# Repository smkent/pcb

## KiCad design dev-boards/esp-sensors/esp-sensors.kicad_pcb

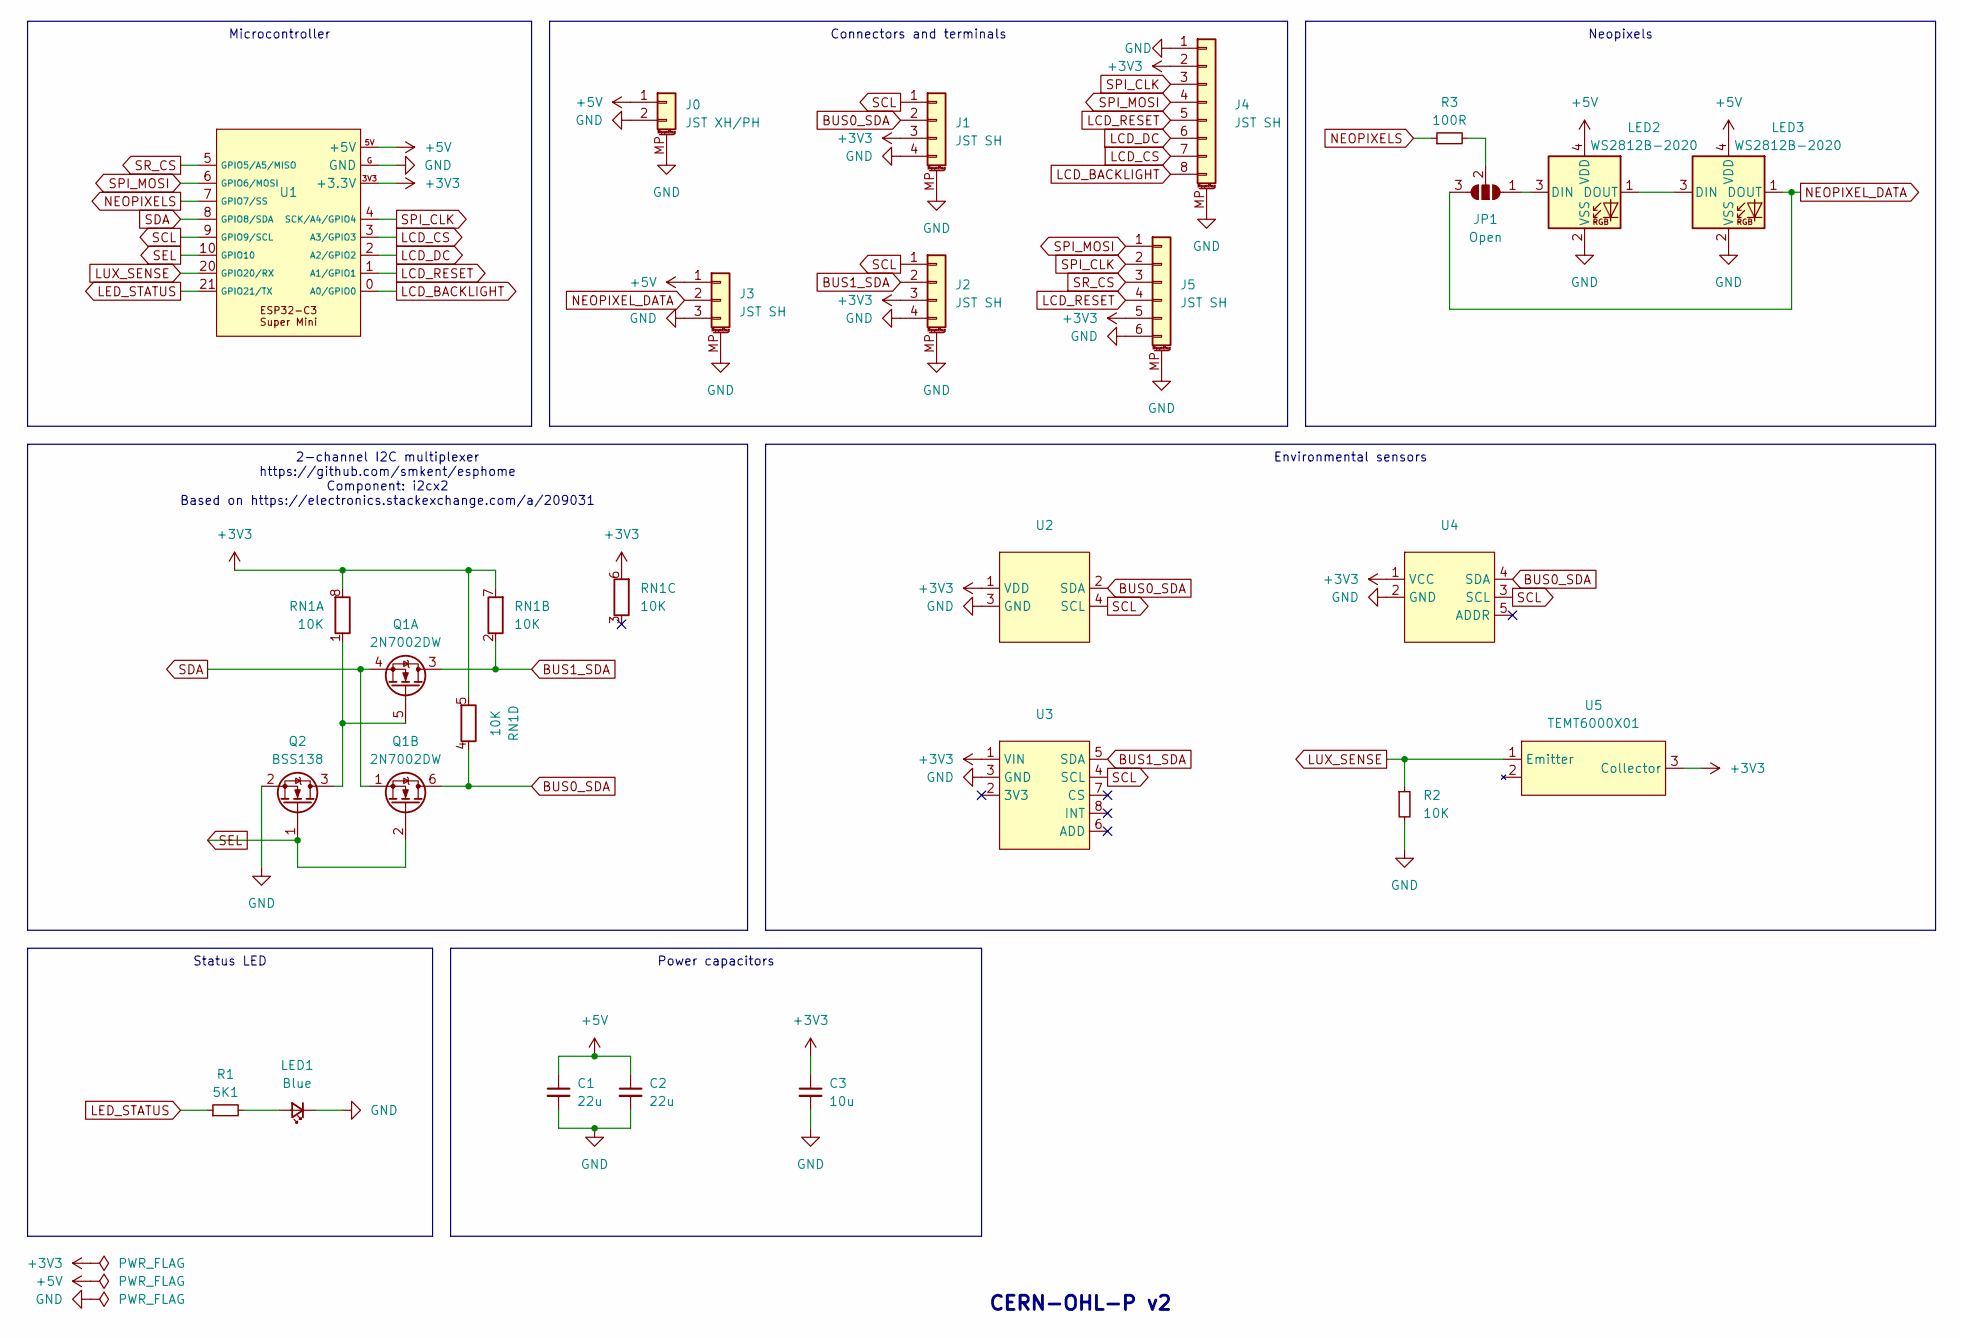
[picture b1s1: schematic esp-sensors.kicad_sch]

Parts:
C1, C2: 22u; C_0805_2012Metric_Pad1.18x1.45mm_HandSolder
C3: 10u; C_0603_1608Metric_Pad1.08x0.95mm_HandSolder
J0: JST XH/PH; Conn_Combo_JST-1x02-XH_PH-SMD-pad2gnd
J1, J2: JST SH; JST_SH_SM04B-SRSS-TB_1x04-1MP_P1.00mm_Horizontal
J3: JST SH; JST_SH_SM03B-SRSS-TB_1x03-1MP_P1.00mm_Horizontal
J4: JST SH; JST_SH_SM08B-SRSS-TB_1x08-1MP_P1.00mm_Horizontal
J5: JST SH; JST_SH_SM06B-SRSS-TB_1x06-1MP_P1.00mm_Horizontal
JP1: Open; SolderJumper-3_P1.3mm_Open_RoundedPad1.0x1.5mm
LED1: Blue; LED_0603_1608Metric_Pad1.05x0.95mm_HandSolder_simple
LED2, LED3: WS2812B-2020; LED-SMD_4P-L2.0-W2.0-BR-1
Q1: 2N7002DW; SOT-23-6; LCSC Part C5190214
Q2: BSS138; SOT-23
R1: 5K1; R_0603_1608Metric_Pad0.98x0.95mm_HandSolder_simple
R2: 10K; R_0603_1608Metric_Pad0.98x0.95mm_HandSolder_simple
R3: 100R; R_0603_1608Metric_Pad0.98x0.95mm_HandSolder
RN1: 10K; R_Array_Convex_4x0603
U1: ESP32-C3-Super-Mini-Castellated-SMD
U2: PinSocket_1x04_P2.54mm_Horizontal_descending_simple
U3: PinSocket_1x08_P2.54mm_Horizontal_descending_simple
U4: PinSocket_1x05_P2.54mm_Horizontal_simple
U5: TEMT6000X01; SENSORS-SMD_TEMT6000X01_HandSolder; LCSC Part C94098

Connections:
+3V3: C3.1, J1.3, J2.3, J4.2, J5.5, RN1.5 (R4.2), RN1.6 (R3.2), RN1.7 (R2.2), RN1.8 (R1.2), U1.3V3 (+3.3V), U2.1 (VDD), U3.1 (VIN), U4.1 (VCC), U5.3 (Collector)
+5V: C1.1, C2.1, J0.1, J3.1, LED2.4 (VDD), LED3.4 (VDD), U1.5V (+5V)
BUS0_SDA: J1.2, Q1.6 (D), RN1.4 (R4.1), U2.2 (SDA), U4.4 (SDA)
BUS1_SDA: J2.2, Q1.3 (D), RN1.2 (R2.1), U3.5 (SDA)
GND: C1.2, C2.2, C3.2, J0.2, J0.MP (MountPin), J1.4, J1.MP (MountPin), J2.4, J2.MP (MountPin), J3.3, J3.MP (MountPin), J4.1, J4.MP (MountPin), J5.6, J5.MP (MountPin), LED1.1 (K), LED2.2 (VSS), LED3.2 (VSS), Q2.2 (S), R2.2, U1.G (GND), U2.3 (GND), U3.3 (GND), U4.2 (GND)
LCD_BACKLIGHT: J4.8, U1.0 (A0/GPIO0)
LCD_CS: J4.7, U1.3 (A3/GPIO3)
LCD_DC: J4.6, U1.2 (A2/GPIO2)
LCD_RESET: J4.5, J5.4, U1.1 (A1/GPIO1)
LED_STATUS: R1.1, U1.21 (GPIO21/TX)
LUX_SENSE: R2.1, U1.20 (GPIO20/RX), U5.1 (Emitter)
NEOPIXELS: R3.1, U1.7 (GPIO7/SS)
NEOPIXEL_DATA: J3.2, JP1.3 (B), LED3.1 (DOUT)
unnamed: JP1.1 (A), LED2.3 (DIN)
unnamed: JP1.2 (C), R3.2
unnamed: LED1.2 (A), R1.2
unnamed: LED2.1 (DOUT), LED3.3 (DIN)
unnamed: Q1.5 (G), Q2.3 (D), RN1.1 (R1.1)
SCL: J1.1, J2.1, U1.9 (GPIO9/SCL), U2.4 (SCL), U3.4 (SCL), U4.3 (SCL)
SDA: Q1.1 (S), Q1.4 (S), U1.8 (GPIO8/SDA)
SEL: Q1.2 (G), Q2.1 (G), U1.10 (GPIO10)
SPI_CLK: J4.3, J5.2, U1.4 (SCK/A4/GPIO4)
SPI_MOSI: J4.4, J5.1, U1.6 (GPIO6/MOSI)
SR_CS: J5.3, U1.5 (GPIO5/A5/MISO)

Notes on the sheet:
2-channel I2C multiplexer https://github.com/smkent/esphome Component: i2cx2 Based on https://electronics.stackexchange.com/a/209031
Environmental sensors
Microcontroller
Power capacitors
Neopixels
Status LED
Connectors and terminals
CERN-OHL-P v2

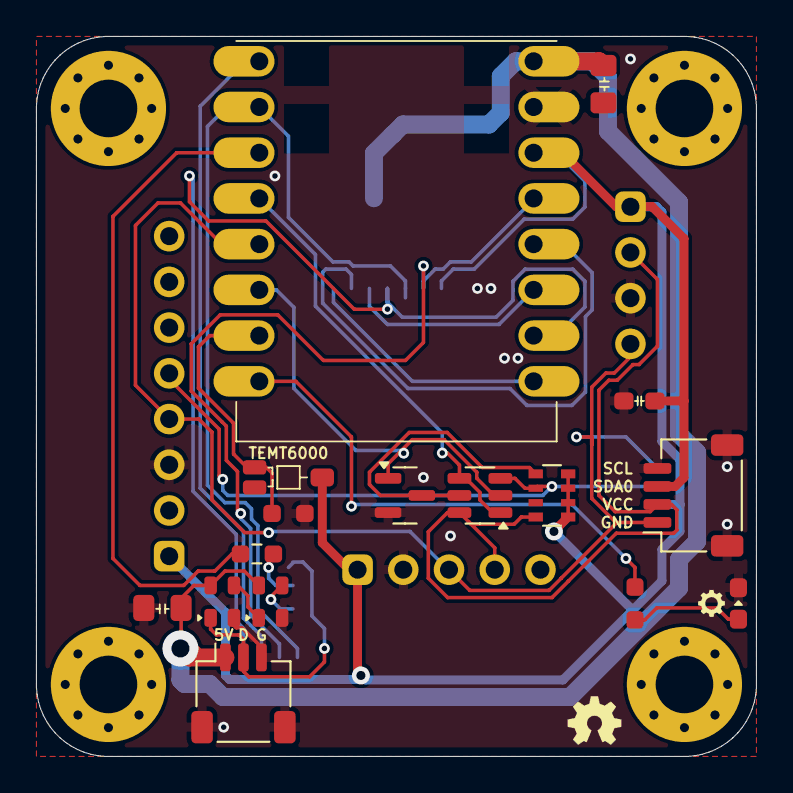
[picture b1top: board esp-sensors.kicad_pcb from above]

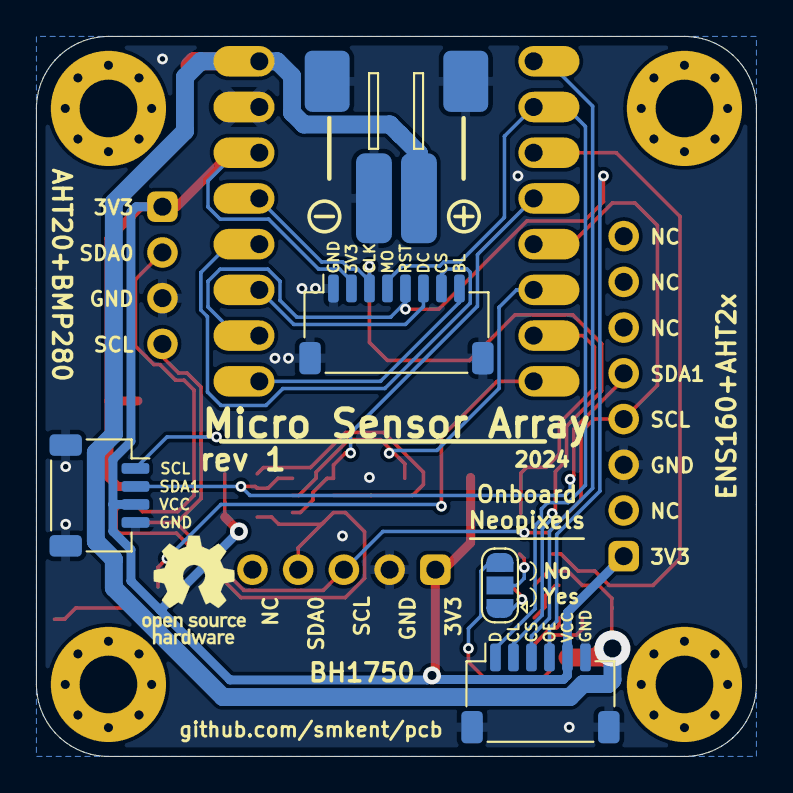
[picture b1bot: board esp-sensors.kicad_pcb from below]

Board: 2 copper layers, 40.0 x 40.0 mm, 24 parts (5 on the bottom side), 24 nets.

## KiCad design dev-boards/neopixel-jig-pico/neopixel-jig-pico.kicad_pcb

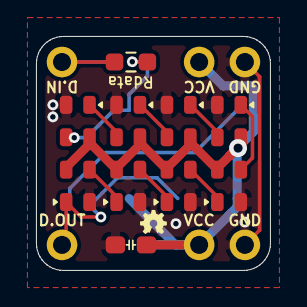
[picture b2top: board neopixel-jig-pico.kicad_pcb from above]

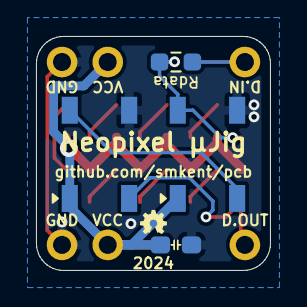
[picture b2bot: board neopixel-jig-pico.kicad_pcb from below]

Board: 2 copper layers, 13.0 x 13.0 mm, 18 parts (8 on the bottom side), 13 nets.

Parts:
C1, C2: 10u; C_0603_1608Metric_Pad1.08x0.95mm_HandSolder
D1, D2: WS2812B; LED_WS2812B_PLCC4_5.0x5.0mm_P3.2mm_simple_small_courtyard
J1, J2: Conn_01x02; PinHeader_1x02_P2.54mm_Vertical_simple
J3, J4: Conn_01x01; PinHeader_1x01_P2.54mm_simple
LED1, LED2, LED3, LED4, LED5, LED6, LED7, LED8: WS2812B-2020; LED-SMD_4P-L2.0-W2.0-BR-1
R1, R2: 100R; R_0603_1608Metric_Pad0.98x0.95mm_HandSolder

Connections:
DATA_2: LED4.1 (DOUT), LED5.3 (DIN)
DATA_IN: D1.4 (DIN), LED1.3 (DIN), R1.2, R2.2
DATA_OUT: D2.2 (DOUT), J4.1, LED8.1 (DOUT)
GND: C1.2, C2.2, D1.3 (VSS), D2.3 (VSS), J1.2, J2.2, LED1.2 (VSS), LED2.2 (VSS), LED3.2 (VSS), LED4.2 (VSS), LED5.2 (VSS), LED6.2 (VSS), LED7.2 (VSS), LED8.2 (VSS)
unnamed: D1.2 (DOUT), D2.4 (DIN)
unnamed: J3.1, R1.1, R2.1
unnamed: LED1.1 (DOUT), LED2.3 (DIN)
unnamed: LED2.1 (DOUT), LED3.3 (DIN)
unnamed: LED3.1 (DOUT), LED4.3 (DIN)
unnamed: LED5.1 (DOUT), LED6.3 (DIN)
unnamed: LED6.1 (DOUT), LED7.3 (DIN)
unnamed: LED7.1 (DOUT), LED8.3 (DIN)
VCC: C1.1, C2.1, D1.1 (VDD), D2.1 (VDD), J1.1, J2.1, LED1.4 (VDD), LED2.4 (VDD), LED3.4 (VDD), LED4.4 (VDD), LED5.4 (VDD), LED6.4 (VDD), LED7.4 (VDD), LED8.4 (VDD)

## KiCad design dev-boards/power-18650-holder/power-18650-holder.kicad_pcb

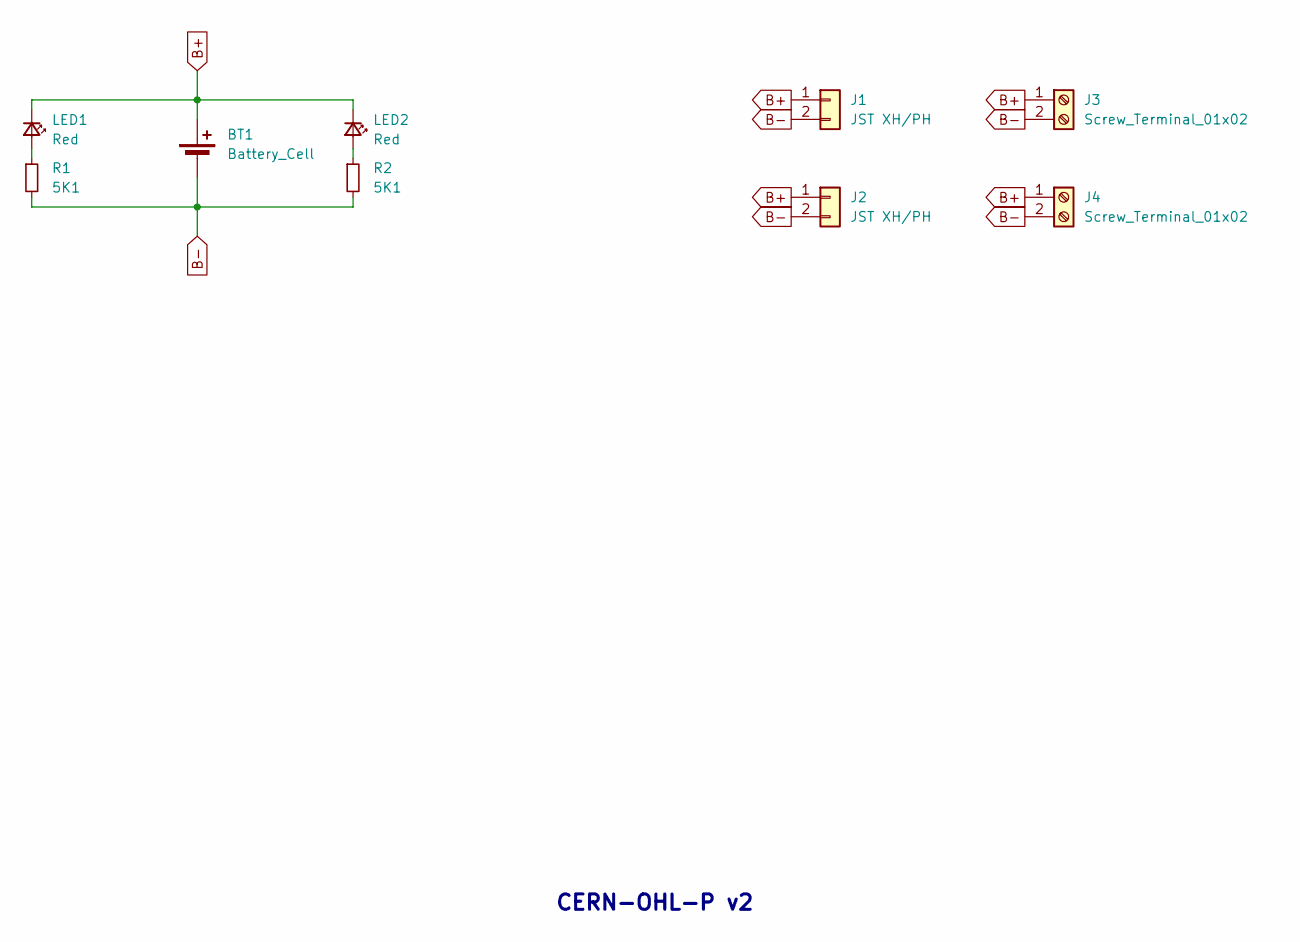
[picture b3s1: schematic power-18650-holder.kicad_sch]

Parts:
BT1: Battery_Cell; BAT-TH_18650-A5BJ001_large_vias
J1, J2: JST XH/PH; Conn_Combo_JST-1x02-XH_PH-THT-pad2gnd
J3, J4: Screw_Terminal_01x02; Conn_Combo_TerminalBlock_P3.5-P5.08_1x02_pad2gnd
LED1, LED2: Red; LED_0603_1608Metric_Pad1.05x0.95mm_HandSolder_simple; LCSC Part C2286
R1, R2: 5K1; R_0603_1608Metric_Pad0.98x0.95mm_HandSolder_simple; LCSC Part C25905

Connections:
B+: BT1.1 (+), J1.1, J2.1, J3.1, J4.1, LED1.1 (K), LED2.1 (K)
B-: BT1.2 (-), J1.2, J2.2, J3.2, J4.2, R1.2, R2.2
unnamed: LED1.2 (A), R1.1
unnamed: LED2.2 (A), R2.1

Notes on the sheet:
CERN-OHL-P v2

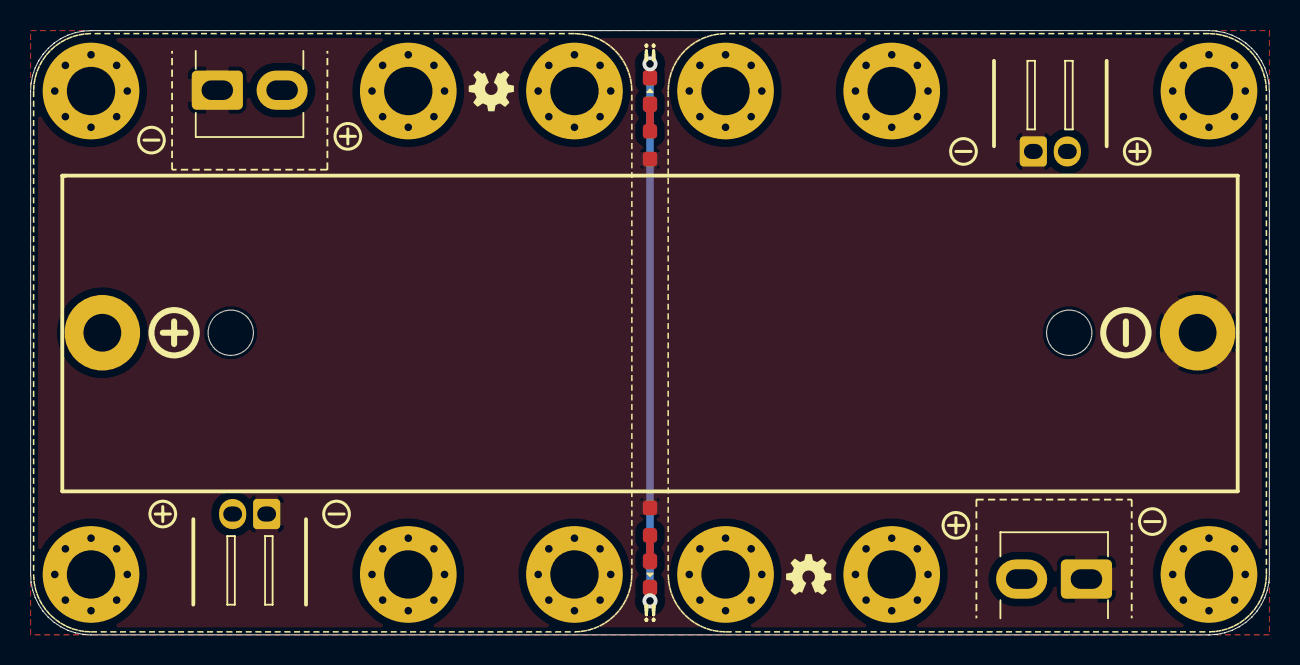
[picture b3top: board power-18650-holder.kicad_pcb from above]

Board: 2 copper layers, 82.0 x 40.0 mm, 9 parts (0 on the bottom side), 4 nets.

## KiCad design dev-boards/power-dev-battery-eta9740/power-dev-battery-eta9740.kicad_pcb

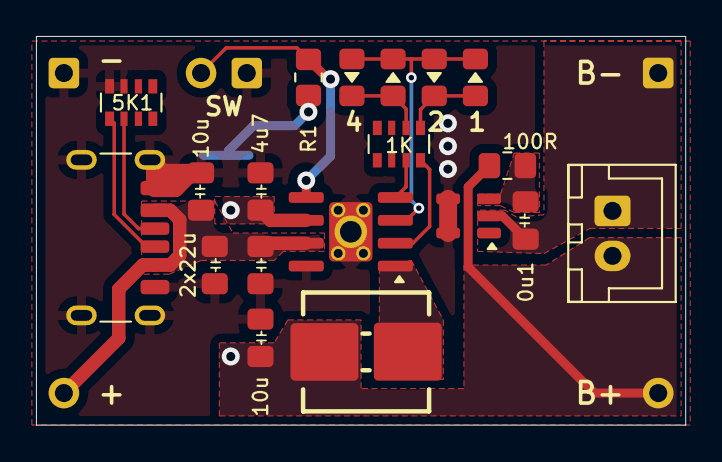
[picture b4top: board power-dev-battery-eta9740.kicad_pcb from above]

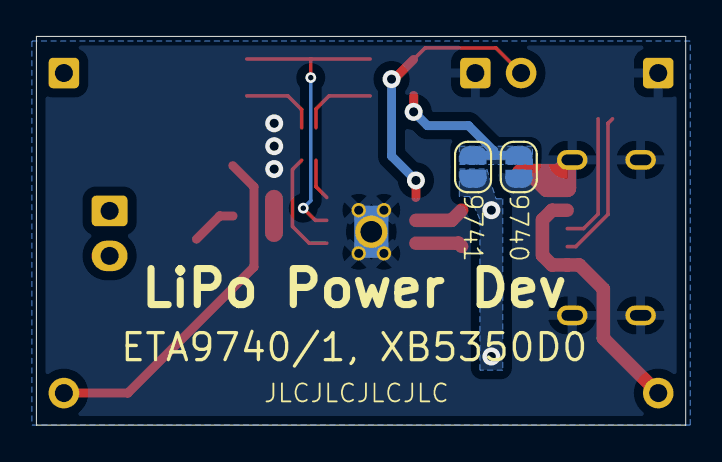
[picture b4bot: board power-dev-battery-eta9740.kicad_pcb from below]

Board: 2 copper layers, 36.1 x 21.6 mm, 26 parts (2 on the bottom side), 15 nets.

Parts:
BT1: Battery_Cell; JST_XH_B2B-XH-A_1x02_P2.50mm_Vertical_simple_pad2gnd
C1: 0.1uF; C_0805_2012Metric_Pad1.18x1.45mm_HandSolder
Cbat1: 4.7uF; C_0805_2012Metric_Pad1.18x1.45mm_HandSolder
Cin1: 10uF; C_0805_2012Metric_Pad1.18x1.45mm_HandSolder
Cout1, Cout2: 22uF; C_0805_2012Metric_Pad1.18x1.45mm_HandSolder
Cusb1: 10uF; C_0805_2012Metric_Pad1.18x1.45mm_HandSolder
J0: USB_C_Receptacle_PowerOnly_6P; USB_C_Receptacle_GCT_USB4125-xx-x_6P_TopMnt_Horizontal_hand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
J1, J3: Conn_01x01; PinHeader_1x01_P2.54mm_simple
J2, J4: Conn_01x01; PinHeader_1x01_P2.54mm_simple_square
JP1, JP2: SolderJumper_2_Open; SolderJumper-2_P1.3mm_Open_RoundedPad1.0x1.5mm
L1: 22uH; Inductor_Multi_7.0x6.6_plus
LED1, LED2, LED3, LED4: LED_0805_2012Metric_Pad1.15x1.40mm_HandSolder_simple
R1: 100K; R_0805_2012Metric_Pad1.20x1.40mm_HandSolder
R2: 100R; R_0805_2012Metric_Pad1.20x1.40mm_HandSolder
RN1: R_Pack04_Split; R_Array_Convex_4x0603
RN2: 5K1; R_Array_Convex_4x0603
SW1: SW_Push; PinHeader_1x02_P2.54mm_Vertical_simple_pad2gnd
U1: ETA9740E8A; SOIC-8-1EP_3.9x4.9mm_P1.27mm_EP2.41x3.3mm_ThermalVias_Custo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
U2: XB5350D0; SOT-23-5_simple

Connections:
0/1_SEL: JP1.2 (B), JP2.1 (A), R1.1
AGND: Cbat1.1, Cin1.1, Cout1.2, Cout2.2, Cusb1.2, J0.A12 (GND), J0.B12 (GND), J0.S1 (SHIELD), J2.1, JP1.1 (A), RN2.7 (R2.2), RN2.8 (R1.2), SW1.2, U1.8 (PGND), U1.9 (AGND), U2.4 (VM), U2.5 (VM)
B+: BT1.1 (+), Cbat1.2, Cin1.2, J3.1, JP2.2 (B), L1.1, R2.1, U1.6 (BAT)
B-: BT1.2 (-), C1.1, J4.1, U2.2 (GND)
BATVDD: C1.2, R2.2, U2.3 (VDD)
ISET: R1.2, SW1.1, U1.5 (ISET)
LED1: RN1.4 (R4.1), U1.2 (LED1)
LED2: LED1.1 (K), LED2.2 (A), LED3.1 (K), LED4.2 (A), U1.3 (LED2)
LED3: RN1.3 (R3.1), U1.4 (LED3)
unnamed: J0.A5 (CC1), RN2.2 (R2.1)
unnamed: J0.B5 (CC2), RN2.1 (R1.1)
unnamed: LED1.2 (A), LED2.1 (K), RN1.5 (R4.2)
unnamed: LED3.2 (A), LED4.1 (K), RN1.6 (R3.2)
SW: L1.2, U1.1 (SW)
VCC: Cout1.1, Cout2.1, Cusb1.1, J0.A9 (VBUS), J0.B9 (VBUS), J1.1, U1.7 (OUT)

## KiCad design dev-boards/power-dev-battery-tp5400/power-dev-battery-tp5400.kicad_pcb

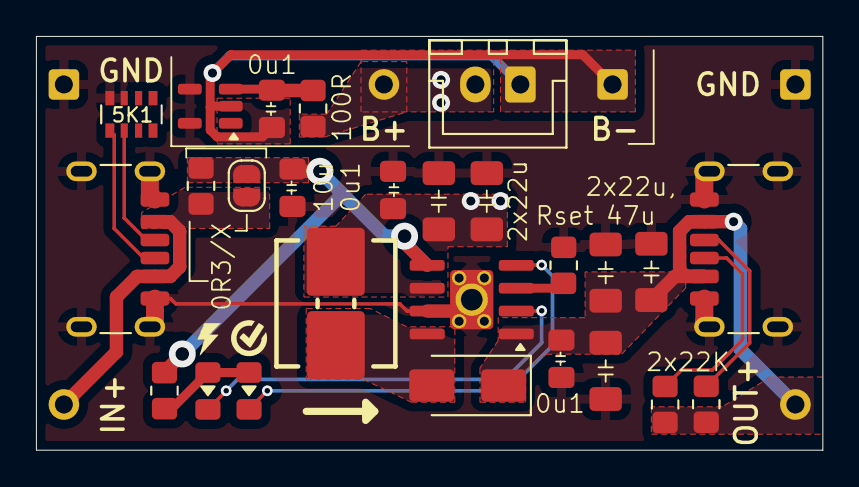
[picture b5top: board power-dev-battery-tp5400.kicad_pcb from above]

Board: 2 copper layers, 43.7 x 23.0 mm, 32 parts (0 on the bottom side), 16 nets.

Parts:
BT1: Battery_Cell; JST_XH_B2B-XH-A_1x02_P2.50mm_Vertical_simple_pad2gnd
C0: 0.1uF; C_0805_2012Metric_Pad1.18x1.45mm_HandSolder
C1: 10u; C_0805_2012Metric_Pad1.18x1.45mm_HandSolder
C2, C5: 0u1; C_0805_2012Metric_Pad1.18x1.45mm_HandSolder
C3, C4, C6, C7: 22u; C_1206_3216Metric_Pad1.33x1.80mm_HandSolder
C8: 47u; C_1206_3216Metric_Pad1.33x1.80mm_HandSolder
D3: SS34; D_SMA
J0, J7: USB_C_Receptacle_PowerOnly_6P; USB_C_Receptacle_GCT_USB4125-xx-x_6P_TopMnt_Horizontal_hand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
J1, J3, J5: Conn_01x01; PinHeader_1x01_P2.54mm_simple
J2, J4, J6: Conn_01x01; PinHeader_1x01_P2.54mm_simple_square
JP1: SolderJumper_2_Open; SolderJumper-2_P1.3mm_Open_RoundedPad1.0x1.5mm
L2: 10u; Inductor_Multi_7.0x6.6_plus
LED1, LED2: LED; LED_0805_2012Metric_Pad1.15x1.40mm_HandSolder_simple
R0: 0R3; R_0805_2012Metric_Pad1.20x1.40mm_HandSolder
R1: 1K; R_0805_2012Metric_Pad1.20x1.40mm_HandSolder
R2: 100R; R_0805_2012Metric_Pad1.20x1.40mm_HandSolder
R3: 1K1; R_0805_2012Metric_Pad1.20x1.40mm_HandSolder
R4, R5: 22K; R_0805_2012Metric_Pad1.20x1.40mm_HandSolder
RN1: 5K1; R_Array_Convex_4x0603
U1: TP5400_C2891434; SOIC-8-1EP_3.9x4.9mm_P1.27mm_EP2.41x3.3mm_ThermalVias_Custo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
U2: XB5350D0; SOT-23-5_simple

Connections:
B+: BT1.1 (+), C2.2, C3.2, C4.2, J3.1, L2.2, R2.1, U1.6 (BAT)
B-: BT1.2 (-), C0.1, J4.1, U2.2 (GND)
BATVDD: C0.2, R2.2, U2.3 (VDD)
GND: C1.1, C2.1, C3.1, C4.1, C5.1, C6.1, C7.1, C8.1, J0.A12 (GND), J0.B12 (GND), J0.S1 (SHIELD), J2.1, J6.1, J7.A12 (GND), J7.B12 (GND), J7.S1 (SHIELD), R3.1, RN1.7 (R2.2), RN1.8 (R1.2), U1.7 (GND), U1.9 (EP), U2.4 (VM), U2.5 (VM)
LED1: LED1.1 (K), U1.2 (~CHRG)
LED2: LED2.1 (K), U1.4 (~STDBY)
LX: D3.2 (A), L2.1, U1.8 (LX)
unnamed: J0.A5 (CC1), RN1.2 (R2.1)
unnamed: J0.B5 (CC2), RN1.1 (R1.1)
unnamed: J7.A5 (CC1), R4.2
unnamed: J7.B5 (CC2), R5.2
unnamed: LED1.2 (A), LED2.2 (A), R1.2
unnamed: R3.2, U1.3 (PROG)
VCC: J0.A9 (VBUS), J0.B9 (VBUS), J1.1, JP1.2 (B), R0.2
VIN: C1.2, JP1.1 (A), R0.1, R1.1, U1.5 (VCC)
VOUT: C5.2, C6.2, C7.2, C8.2, D3.1 (K), J5.1, J7.A9 (VBUS), J7.B9 (VBUS), R4.1, R5.1, U1.1 (VOUT)

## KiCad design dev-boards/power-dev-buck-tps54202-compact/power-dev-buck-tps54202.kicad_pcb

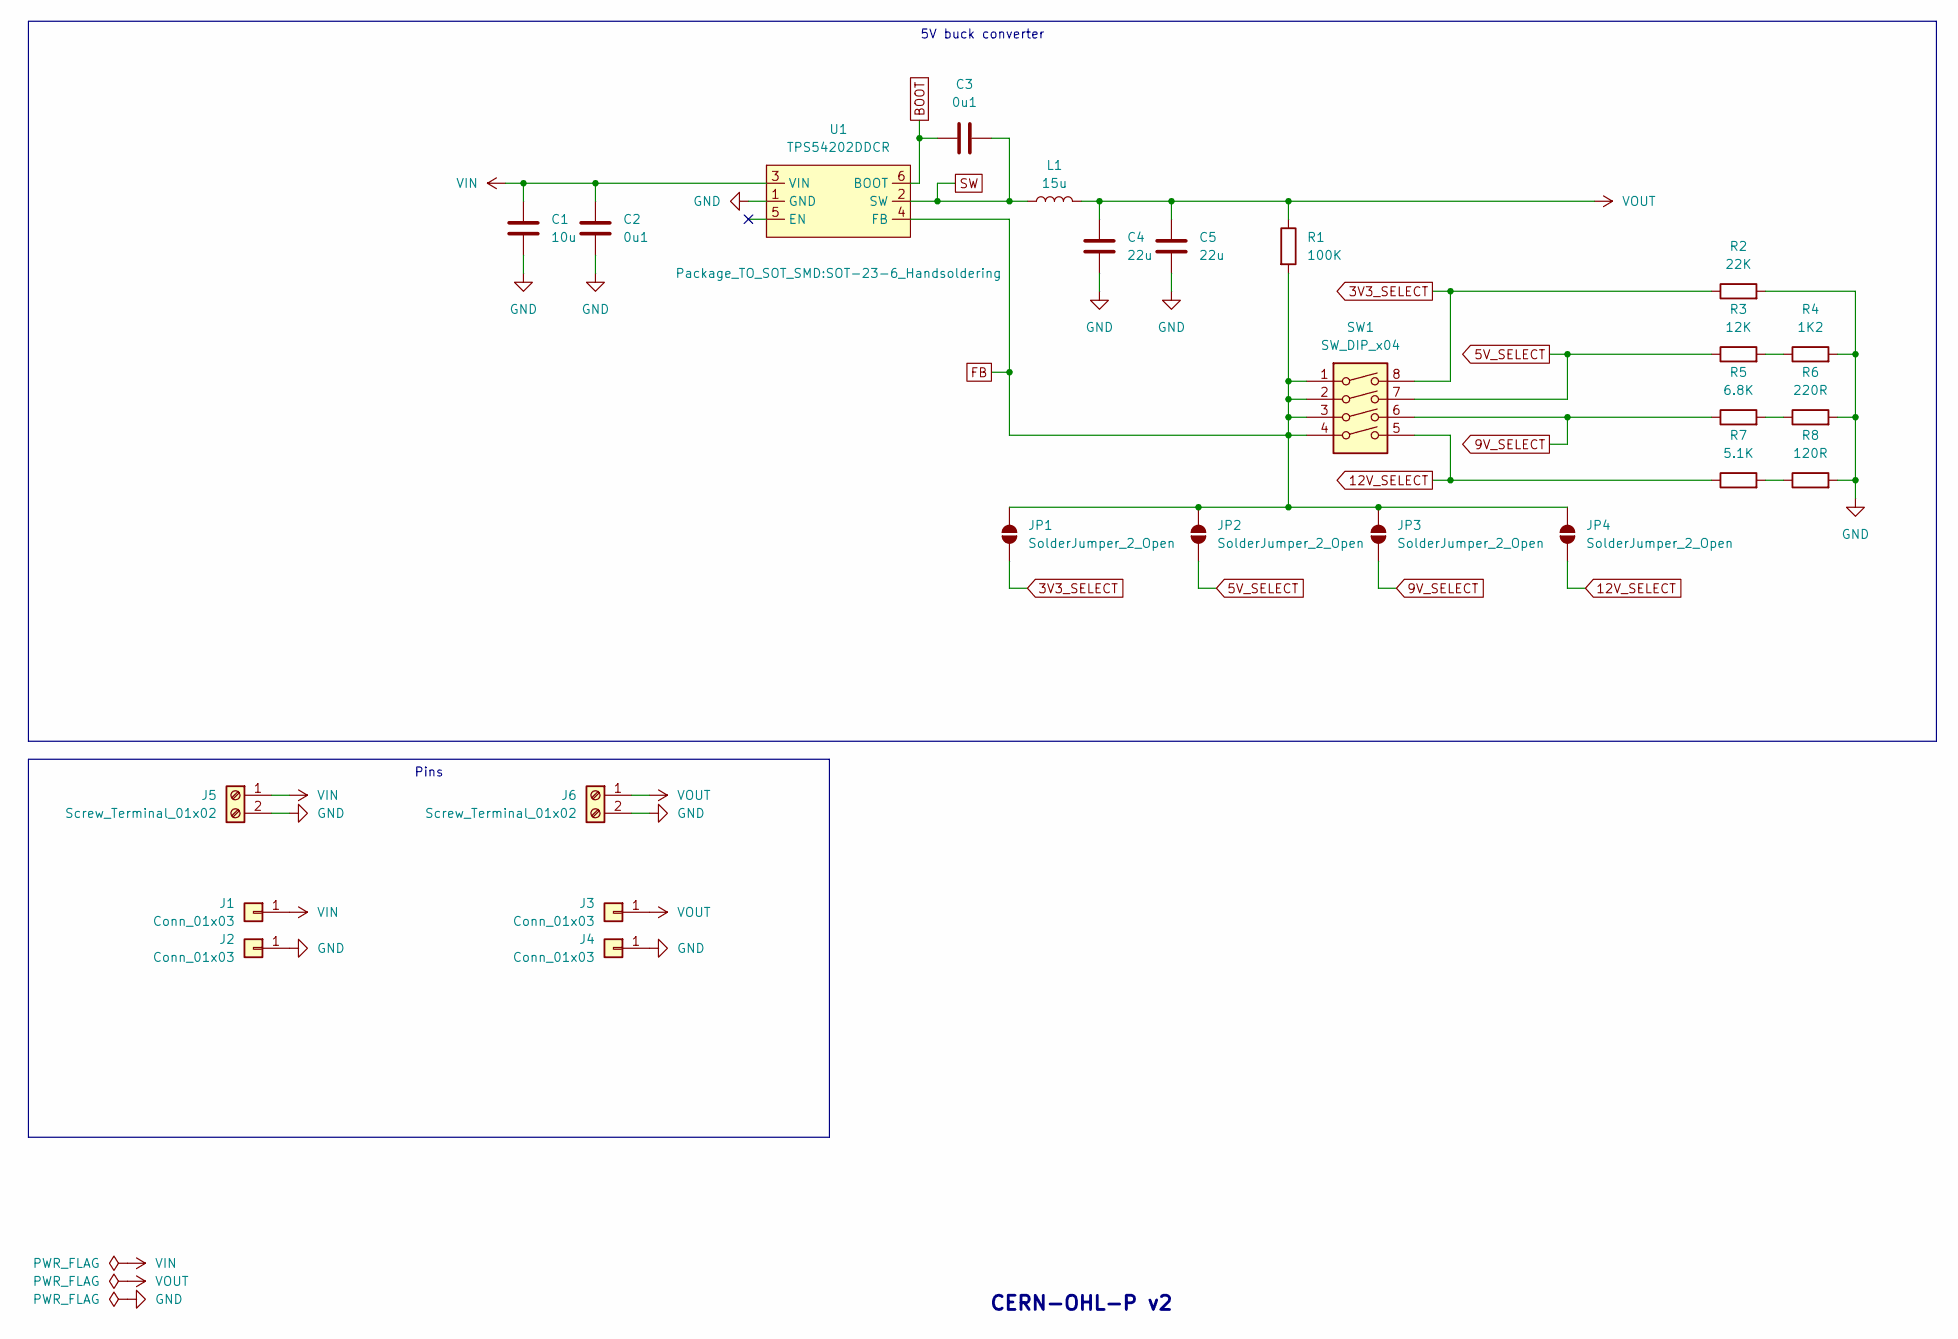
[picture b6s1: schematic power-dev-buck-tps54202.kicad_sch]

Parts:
C1: 10u; C_0805_2012Metric_Pad1.18x1.45mm_HandSolder; LCSC Part C440198
C2, C3: 0u1; C_0402_1005Metric; LCSC Part C307331
C4, C5: 22u; C_0805_2012Metric_Pad1.18x1.45mm_HandSolder; LCSC Part C45783
J1, J3: Conn_01x03; PinHeader_1x01_P2.54mm_simple
J2, J4: Conn_01x03; PinHeader_1x01_P2.54mm_simple_square
J5, J6: Screw_Terminal_01x02; TerminalBlock_or_JST_2.54_1x02
JP1, JP2, JP3, JP4: SolderJumper_2_Open; SolderJumper-2_P1.3mm_Open_RoundedPad1.0x1.5mm_simple
L1: 15u; Inductor_Multi_5.2x5.7_2x2.5
R1: 100K; R_0402_1005Metric; LCSC Part C25741
R2: 22K; R_0402_1005Metric; LCSC Part C25768
R3: 12K; R_0402_1005Metric; LCSC Part C25752
R4: 1K2; R_0402_1005Metric; LCSC Part C25862
R5: 6.8K; R_0402_1005Metric; LCSC Part C25917
R6: 220R; R_0402_1005Metric; LCSC Part C25091
R7: 5.1K; R_0402_1005Metric; LCSC Part C25905
R8: 120R; R_0402_1005Metric; LCSC Part C25079
SW1: SW_DIP_x04; SW_DIP_SPSTx04_Slide_P1.27mm_simple
U1: TPS54202DDCR; SOT-23-6_Handsoldering; LCSC Part C191884

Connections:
3V3_SELECT: JP1.1 (A), R2.1, SW1.8
5V_SELECT: JP2.1 (A), R3.1, SW1.7
9V_SELECT: JP3.1 (A), R5.1, SW1.6
12V_SELECT: JP4.1 (A), R7.1, SW1.5
BOOT: C3.1, U1.6 (BOOT)
FB: JP1.2 (B), JP2.2 (B), JP3.2 (B), JP4.2 (B), R1.2, SW1.1, SW1.2, SW1.3, SW1.4, U1.4 (FB)
GND: C1.2, C2.2, C4.2, C5.2, J2.1, J4.1, J5.2, J6.2, R2.2, R4.2, R6.2, R8.2, U1.1 (GND)
unnamed: R3.2, R4.1
unnamed: R5.2, R6.1
unnamed: R7.2, R8.1
SW: C3.2, L1.1, U1.2 (SW)
VIN: C1.1, C2.1, J1.1, J5.1, U1.3 (VIN)
VOUT: C4.1, C5.1, J3.1, J6.1, L1.2, R1.1

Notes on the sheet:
5V buck converter
Pins
CERN-OHL-P v2

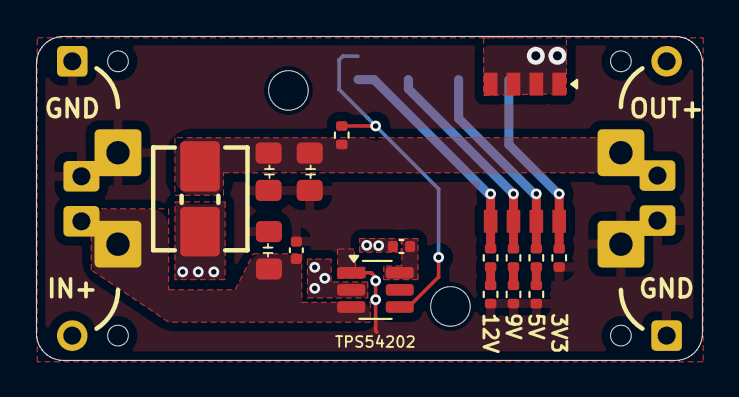
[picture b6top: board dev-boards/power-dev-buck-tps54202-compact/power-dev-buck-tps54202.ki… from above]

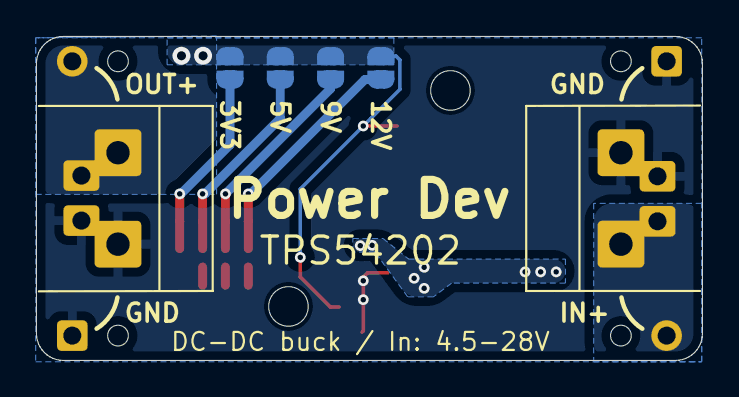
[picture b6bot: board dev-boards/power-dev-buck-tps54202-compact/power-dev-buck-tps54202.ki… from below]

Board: 2 copper layers, 37.0 x 18.0 mm, 26 parts (10 on the bottom side), 13 nets.

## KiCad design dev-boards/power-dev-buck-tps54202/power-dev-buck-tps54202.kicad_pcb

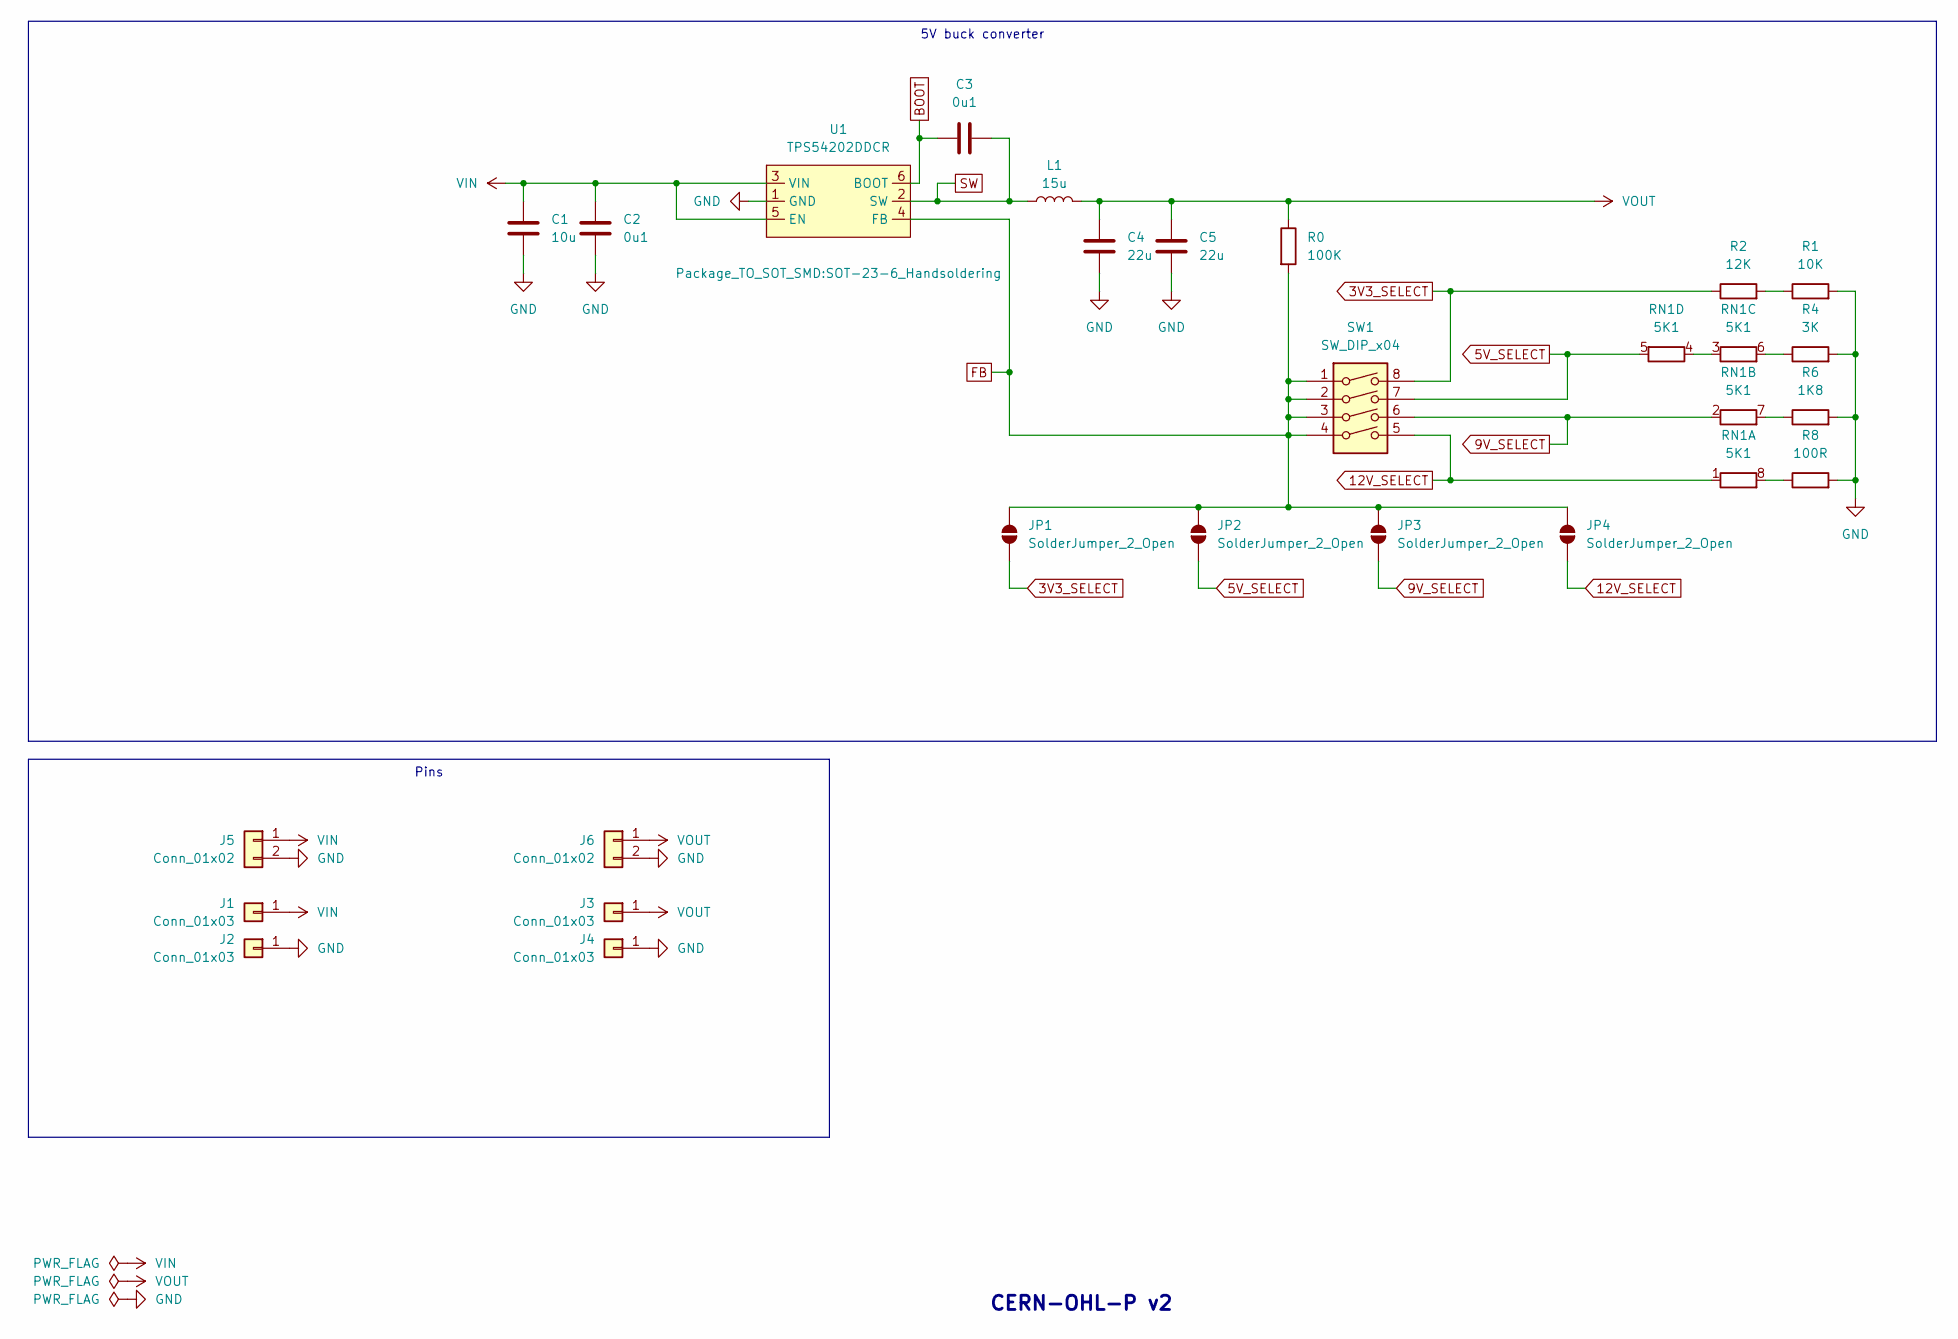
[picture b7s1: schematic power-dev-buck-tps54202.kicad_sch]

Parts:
C1: 10u; C_0805_2012Metric_Pad1.18x1.45mm_HandSolder; LCSC Part C440198
C2, C3: 0u1; C_0805_2012Metric_Pad1.18x1.45mm_HandSolder
C4, C5: 22u; C_0805_2012Metric_Pad1.18x1.45mm_HandSolder; LCSC Part C45783
J1, J3: Conn_01x03; PinHeader_1x01_P2.54mm_simple
J2, J4: Conn_01x03; PinHeader_1x01_P2.54mm_simple_square
J5, J6: Conn_01x02; JST_XH_S2B-XH-2AW_1x02_P2.50mm_pad2gnd_trim2
JP1, JP2, JP3, JP4: SolderJumper_2_Open; SolderJumper-2_P1.3mm_Open_RoundedPad1.0x1.5mm_simple
L1: 15u; Inductor_Multi_7.0x6.6_plus
R0: 100K; R_0805_2012Metric_Pad1.20x1.40mm_HandSolder
R1: 10K; R_0805_2012Metric_Pad1.20x1.40mm_HandSolder
R2: 12K; R_0805_2012Metric_Pad1.20x1.40mm_HandSolder
R4: 3K; R_0805_2012Metric_Pad1.20x1.40mm_HandSolder
R6: 1K8; R_0805_2012Metric_Pad1.20x1.40mm_HandSolder
R8: 100R; R_0805_2012Metric_Pad1.20x1.40mm_HandSolder
RN1: 5K1; R_Array_Convex_4x0603
SW1: SW_DIP_x04; SW_DIP_SPSTx04_Slide_P1.27mm_simple
U1: TPS54202DDCR; SOT-23-6_Handsoldering; LCSC Part C191884

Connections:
3V3_SELECT: JP1.1 (A), R2.1, SW1.8
5V_SELECT: JP2.1 (A), RN1.5 (R4.2), SW1.7
9V_SELECT: JP3.1 (A), RN1.2 (R2.1), SW1.6
12V_SELECT: JP4.1 (A), RN1.1 (R1.1), SW1.5
BOOT: C3.1, U1.6 (BOOT)
FB: JP1.2 (B), JP2.2 (B), JP3.2 (B), JP4.2 (B), R0.2, SW1.1, SW1.2, SW1.3, SW1.4, U1.4 (FB)
GND: C1.2, C2.2, C4.2, C5.2, J2.1, J4.1, J5.2, J6.2, R1.2, R4.2, R6.2, R8.2, U1.1 (GND)
unnamed: R1.1, R2.2
unnamed: R8.1, RN1.8 (R1.2)
unnamed: R6.1, RN1.7 (R2.2)
unnamed: RN1.3 (R3.1), RN1.4 (R4.1)
unnamed: R4.1, RN1.6 (R3.2)
SW: C3.2, L1.1, U1.2 (SW)
VIN: C1.1, C2.1, J1.1, J5.1, U1.3 (VIN), U1.5 (EN)
VOUT: C4.1, C5.1, J3.1, J6.1, L1.2, R0.1

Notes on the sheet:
5V buck converter
Pins
CERN-OHL-P v2

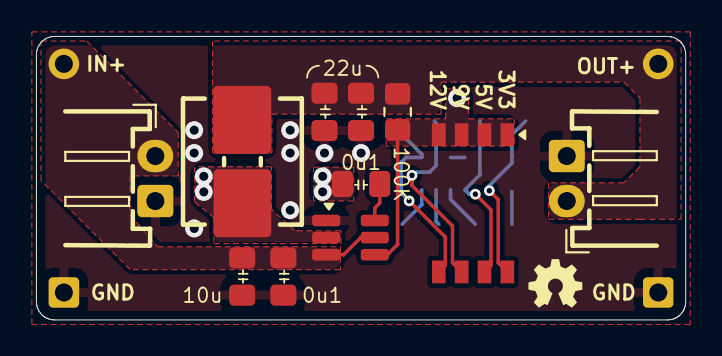
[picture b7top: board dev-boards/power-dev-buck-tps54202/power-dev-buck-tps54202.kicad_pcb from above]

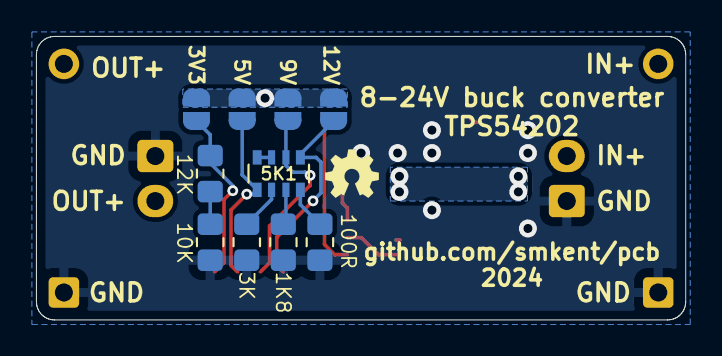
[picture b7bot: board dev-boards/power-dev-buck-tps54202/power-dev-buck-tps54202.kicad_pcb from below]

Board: 2 copper layers, 36.1 x 15.7 mm, 25 parts (14 on the bottom side), 15 nets.

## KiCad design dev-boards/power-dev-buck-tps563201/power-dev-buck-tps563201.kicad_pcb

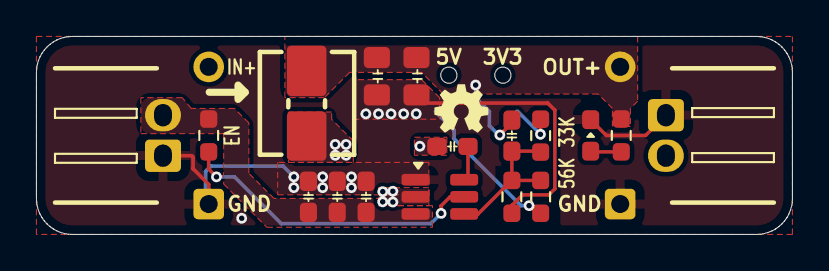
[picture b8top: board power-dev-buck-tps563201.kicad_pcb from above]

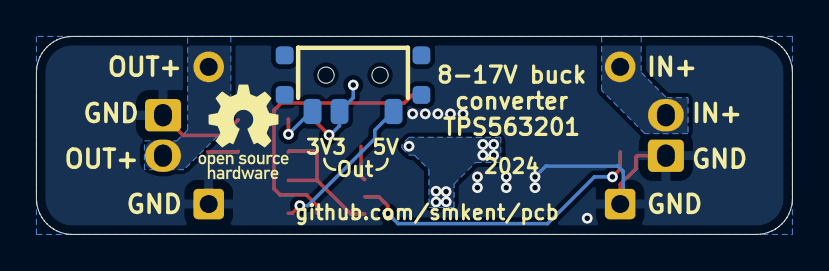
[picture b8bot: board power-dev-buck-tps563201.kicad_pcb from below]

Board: 2 copper layers, 42.0 x 11.0 mm, 22 parts (5 on the bottom side), 10 nets.

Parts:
C1, C2: 10u; C_0603_1608Metric_Pad1.08x0.95mm_HandSolder
C3, C7: 0u1; C_0603_1608Metric_Pad1.08x0.95mm_HandSolder
C4: 75p; C_0603_1608Metric_Pad1.08x0.95mm_HandSolder
C8, C9: 22u; C_0805_2012Metric_Pad1.18x1.45mm_HandSolder
J1, J4: Conn_01x02; Conn_Combo_JST-1x02-XH_PH-THT-pad2gnd
J2, J5: Conn_01x03; PinHeader_1x01_P2.54mm_simple
J3, J6: Conn_01x03; PinHeader_1x01_P2.54mm_simple_square
L1: 4u7; Inductor_Multi_5.2x5.7_2x2.5
LED1: LED_Small; LED_0603_1608Metric_Pad1.05x0.95mm_HandSolder_simple
R0, R1, R4: 10K; R_0603_1608Metric_Pad0.98x0.95mm_HandSolder
R2: 56K; R_0603_1608Metric_Pad0.98x0.95mm_HandSolder
R3: 33K; R_0603_1608Metric_Pad0.98x0.95mm_HandSolder
SW1: SW_SPDT; SW-SMD_3P-P1.50_L2.7-W6.6
U1: TPS563200; SOT-23-6_Handsoldering_simple

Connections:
FB: C4.1, R1.2, R2.1, R3.2, U1.4 (VFB)
GND: C1.2, C2.2, C3.2, C8.2, C9.2, J1.2, J3.1, J4.2, J6.1, LED1.1 (K), R1.1, U1.1 (GND)
unnamed: LED1.2 (A), R0.1
unnamed: R2.2, SW1.1 (A)
unnamed: R3.1, SW1.3 (C)
unnamed: R4.2, U1.5 (EN)
unnamed: C7.1, U1.6 (VBST)
SW: C7.2, L1.1, U1.2 (SW)
VIN: C1.1, C2.1, C3.1, J1.1, J2.1, R4.1, U1.3 (VIN)
VOUT: C4.2, C8.1, C9.1, J4.1, J5.1, L1.2, R0.2, SW1.2 (B)
